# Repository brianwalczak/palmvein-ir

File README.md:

# palmvein-ir

An all-in-one IR illumination board for palm vein imaging, built using 16 high-power 860nm LEDs in two independently controlled channels.

## Why?

I built this board to serve as a second, more complete iteration of my original ir-led-board design [here](https://github.com/brianwalczak/ir-led-board). The main limitation of the first iteration was that it used 16 low-current IR LEDs, which made images less detailed because the infrared light didn't penetrate the palm effectively. The images were good for a proof-of-concept neural network but lacked the detail needed for a high detection accuracy. The square design also didn't accurately reflect the shape of an actual palm.

Another issue was the camera cutout. I decided to switch to the OV9281 for its global shutter and lack of a Bayer filter (which makes it the better camera for IR imaging). However, it uses a longer barrel lens, so the board needed a larger, circular camera cutout.

The board also lacked a position sensor, which made it difficult to calculate the palm's distance from the camera. For this first prototype, I tried to estimate palm distance using the average dimensions of a human palm, but I found out it was very unreliable, especially among varying age groups. I found that a distance sensor is the most reliable solution because adding an algorithm that estimates age range would honestly be way overengineered (and still unreliable among some people).

Finally, I added a dedicated microcontroller to handle the LED processing separately from the Raspberry Pi, which allows for precise LED flickering and switching without being affected by Linux delays!

## Features

I designed this board as an all-in-one solution to power and control the infrared LEDs, handle distance calculations, and to power the Raspberry Pi:

- 16x 860nm IR LEDs (OSRAM SFH 4718A) in two independently controlled channels
- Constant-current drivers (AL8861Y-13) with PWM brightness control, both running at about 909 mA
- Microcontroller (CH32V003) for LED control and channel switching
- Time-of-flight distance sensor (VL53L4CDV0DH/1) for measuring the palm's distance from the camera
- USB-C PD power at 20V, which also powers the Raspberry Pi 5 through a 5V buck converter
- Surge protector and eFuse for overvoltage and overcurrent protection

I chose USB-C over a fixed DC power supply because it's easier to use and more compact. The Raspberry Pi is powered through a custom JST cable connected to its 5V pins.

## Bill of Materials (BOM)

The key components for this project are listed below, but you can find the full BOM (including capacitors, resistors, etc.) [here](bom.csv).

| Qty | Component | Part |
|----:|-----------|------|
| 16 | 860nm IR LED | OSRAM SFH 4718A |
| 1 | Microcontroller | CH32V003A4M6 |
| 1 | Distance sensor | VL53L4CDV0DH/1 |
| 1 | USB-C PD trigger | CH224A |
| 1 | Pi buck converter (5V, 5A) | SY8366HQQC |
| 1 | 3.3V regulator | AMS1117-3.3 |
| 2 | LED driver | AL8861Y-13 |
| 1 | eFuse | MX25947ES |
| 1 | Surge protector (TDS) | TDS2211P.C(ES) |
| 1 | USB-C port | TYPE-C-31-M-12 |
| 1 | JST VH 6-pin connector | S6P-VH(LF)(SN)(P) |
| 1 | 4-pin programming header | PZ2.54-1x4PWZ-L13.8-A |

**Not included:** Raspberry Pi 5, OV9281-110 Camera, and a 65W+ USB-C PD charger.

## AI Usage

I used Claude Opus 5.5 to assist in routing the PCB, and to apply a few design fixes during the routing step.

## License

All hardware design files are released under the [CERN-OHL-P-2.0](LICENSE) license! Symbols, footprints, and 3D models were imported from EasyEDA using JLCImport and are not covered by this license.

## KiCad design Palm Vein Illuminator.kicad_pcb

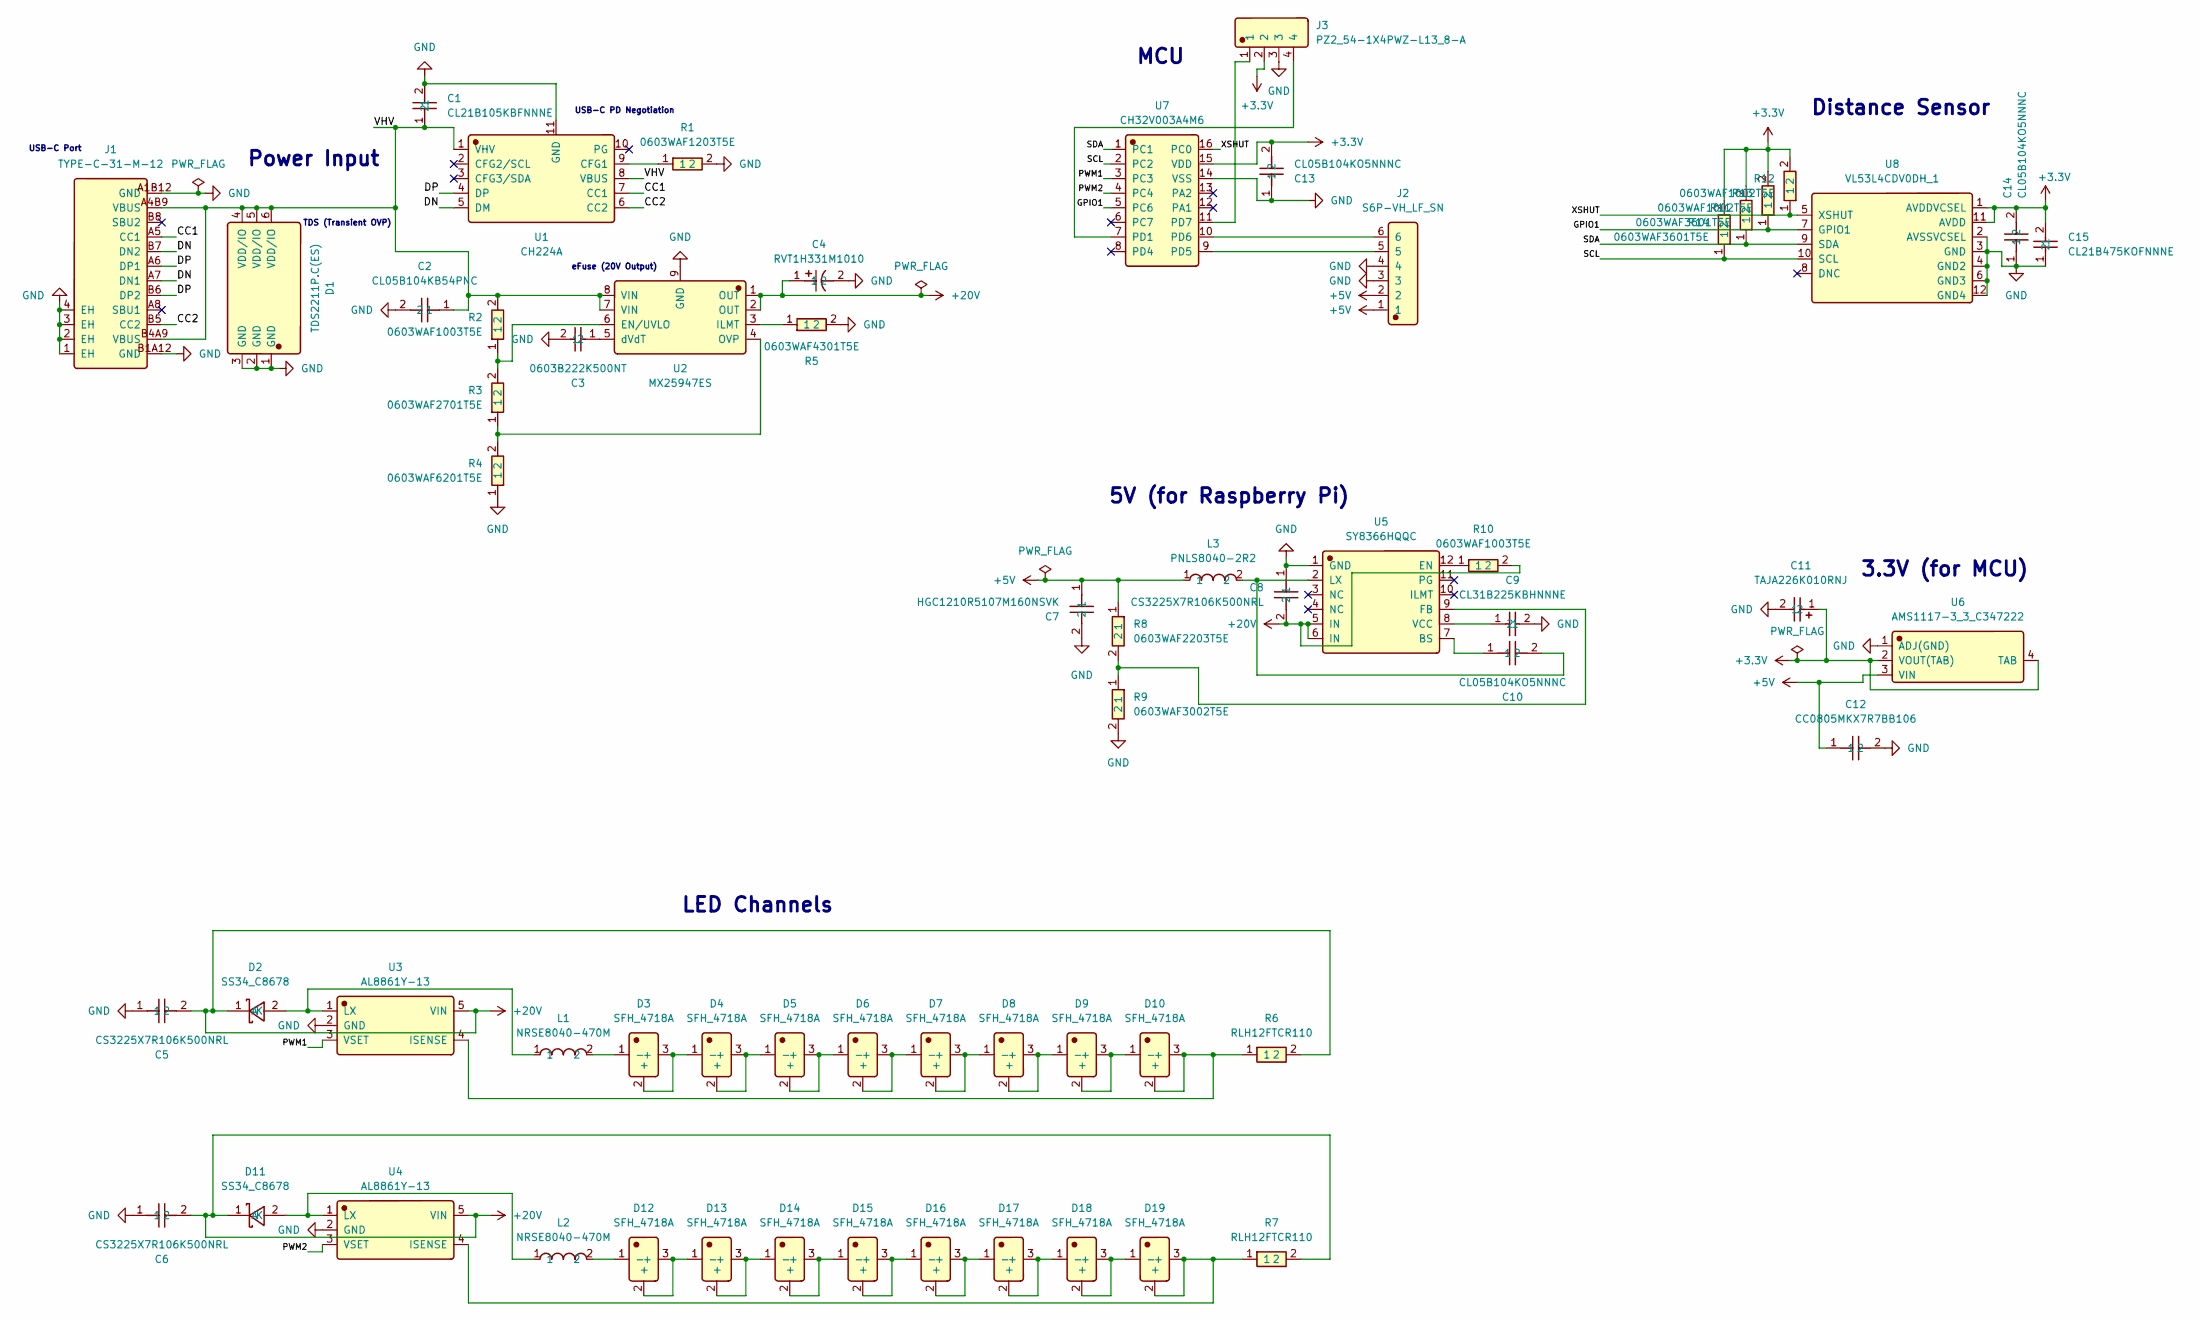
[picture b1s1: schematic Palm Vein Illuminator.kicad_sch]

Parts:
C1: CL21B105KBFNNNE; Manufacturer Part CL21B105KBFNNNE; LCSC C28323
C2: CL05B104KB54PNC; Manufacturer Part CL05B104KB54PNC; LCSC C307331
C3: 0603B222K500NT; Manufacturer Part 0603B222K500NT; LCSC C1604
C4: RVT1H331M1010; Manufacturer Part RVT1H331M1010 330UF 50V; LCSC C2687701
C5, C6, C8: CS3225X7R106K500NRL; Manufacturer Part CS3225X7R106K500NRL; LCSC C2918502
C7: HGC1210R5107M160NSVK; Manufacturer Part HGC1210R5107M160NSVK; LCSC C7432790
C9: CL31B225KBHNNNE; Manufacturer Part CL31B225KBHNNNE; LCSC C50254
C10, C13, C14: CL05B104KO5NNNC; Manufacturer Part CL05B104KO5NNNC; LCSC C1525
C11: TAJA226K010RNJ; Manufacturer Part TAJA226K010RNJ; LCSC C11366
C12: CC0805MKX7R7BB106; Manufacturer Part CC0805MKX7R7BB106; LCSC C1952587
C15: CL21B475KOFNNNE; Manufacturer Part CL21B475KOFNNNE; LCSC C107365
D1: TDS2211P.C(ES); Manufacturer Part TDS2211P.C(ES); LCSC C49108767
D2, D11: SS34_C8678; Manufacturer Part SS34; LCSC C8678
D3, D4, D5, D6, D7, D8, D9, D10, D12, D13, D14, D15, D16, D17, D18, D19: SFH_4718A; Manufacturer Part SFH 4718A; LCSC C2900417
J1: TYPE-C-31-M-12; Manufacturer Part TYPE-C-31-M-12; LCSC C165948
J2: S6P-VH_LF_SN; Manufacturer Part S6P-VH(LF)(SN)(P); LCSC C495698
J3: PZ2_54-1X4PWZ-L13_8-A; Manufacturer Part PZ2.54-1x4PWZ-L13.8-A; LCSC C54907647
L1, L2: NRSE8040-470M; Manufacturer Part NRSE8040-470M; LCSC C2903105
L3: PNLS8040-2R2; Manufacturer Part PNLS8040-2R2M 2.2UH; LCSC C2849550
R1: 0603WAF1203T5E; Manufacturer Part 0603WAF1203T5E; LCSC C25808
R2, R10: 0603WAF1003T5E; Manufacturer Part 0603WAF1003T5E; LCSC C25803
R3: 0603WAF2701T5E; Manufacturer Part 0603WAF2701T5E; LCSC C13167
R4: 0603WAF6201T5E; Manufacturer Part 0603WAF6201T5E; LCSC C4260
R5: 0603WAF4301T5E; Manufacturer Part 0603WAF4301T5E; LCSC C23159
R6, R7: RLH12FTCR110; Manufacturer Part RLH12FTCR110; LCSC C22464898
R8: 0603WAF2203T5E; Manufacturer Part 0603WAF2203T5E; LCSC C22961
R9: 0603WAF3002T5E; Manufacturer Part 0603WAF3002T5E; LCSC C22984
R11, R14: 0603WAF3601T5E; Manufacturer Part 0603WAF3601T5E; LCSC C22980
R12, R13: 0603WAF1002T5E; Manufacturer Part 0603WAF1002T5E; LCSC C25804
U1: CH224A; Manufacturer Part CH224A; LCSC C42459160
U2: MX25947ES; Manufacturer Part MX25947ES; LCSC C5875698
U3, U4: AL8861Y-13; Manufacturer Part AL8861Y-13; LCSC C507867
U5: SY8366HQQC; Manufacturer Part SY8366HQQC; LCSC C178253
U6: AMS1117-3_3_C347222; Manufacturer Part AMS1117-3.3; LCSC C347222
U7: CH32V003A4M6; Manufacturer Part CH32V003A4M6; LCSC C5346357
U8: VL53L4CDV0DH_1; Manufacturer Part VL53L4CDV0DH/1; LCSC C3178291

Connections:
+3.3V: C11.1, C13.2, C14.2, C15.2, J3.2, R11.2, R12.2, R13.2, R14.2, U6.2 (VOUT(TAB)), U6.4 (TAB), U7.15 (VDD), U8.1 (AVDDVCSEL), U8.11 (AVDD)
+5V: C7.1, C12.1, J2.1, J2.2, L3.1, R8.1, U6.3 (VIN)
+20V: C4.1, C5.2, C6.2, C8.2, D2.1 (K), D11.1 (K), R6.2, R7.2, R10.2, U2.1 (OUT), U2.2 (OUT), U3.5 (VIN), U4.5 (VIN), U5.5 (IN), U5.6 (IN)
/CC1: J1.A5 (CC1), U1.7 (CC1)
/CC2: J1.B5 (CC2), U1.6 (CC2)
/DN: J1.A7 (DN1), J1.B7 (DN2), U1.5 (DM)
/DP: J1.A6 (DP1), J1.B6 (DP2), U1.4 (DP)
/GPIO1: R13.1, U7.5 (PC6), U8.7 (GPIO1)
/PWM1: U3.3 (VSET), U7.3 (PC3)
/PWM2: U4.3 (VSET), U7.4 (PC4)
/SCL: R14.1, U7.2 (PC2), U8.10 (SCL)
/SDA: R11.1, U7.1 (PC1), U8.9 (SDA)
/VHV: C1.1, C2.1, D1.4 (VDD/IO), D1.5 (VDD/IO), D1.6 (VDD/IO), J1.A4B9 (VBUS), J1.B4A9 (VBUS), R2.2, U1.1 (VHV), U1.8 (VBUS), U2.7 (VIN), U2.8 (VIN)
/XSHUT: R12.1, U7.16 (PC0), U8.5 (XSHUT)
GND: C1.2, C2.2, C3.2, C4.2, C5.1, C6.1, C7.2, C8.1, C9.2, C11.2, C12.2, C13.1, C14.1, C15.1, D1.1 (GND), D1.2 (GND), D1.3 (GND), J1.1 (EH), J1.2 (EH), J1.3 (EH), J1.4 (EH), J1.A1B12 (GND), J1.B1A12 (GND), J2.3, J2.4, J3.3, R1.2, R4.1, R5.2, R9.2, U1.11 (GND), U2.9 (GND), U3.2 (GND), U4.2 (GND), U5.1 (GND), U6.1 (ADJ(GND)), U7.14 (VSS), U8.2 (AVSSVCSEL), U8.3 (GND), U8.4 (GND2), U8.6 (GND3), U8.12 (GND4)
unnamed: D2.2 (A), L1.1, U3.1 (LX)
unnamed: D3.1 (-), L1.2
unnamed: D3.2 (+), D3.3 (+), D4.1 (-)
unnamed: D4.2 (+), D4.3 (+), D5.1 (-)
unnamed: D5.2 (+), D5.3 (+), D6.1 (-)
unnamed: D6.2 (+), D6.3 (+), D7.1 (-)
unnamed: D7.2 (+), D7.3 (+), D8.1 (-)
unnamed: D8.2 (+), D8.3 (+), D9.1 (-)
unnamed: D9.2 (+), D9.3 (+), D10.1 (-)
unnamed: D11.2 (A), L2.1, U4.1 (LX)
unnamed: D12.1 (-), L2.2
unnamed: D12.2 (+), D12.3 (+), D13.1 (-)
unnamed: D13.2 (+), D13.3 (+), D14.1 (-)
unnamed: D14.2 (+), D14.3 (+), D15.1 (-)
unnamed: D15.2 (+), D15.3 (+), D16.1 (-)
unnamed: D16.2 (+), D16.3 (+), D17.1 (-)
unnamed: D17.2 (+), D17.3 (+), D18.1 (-)
unnamed: D18.2 (+), D18.3 (+), D19.1 (-)
unnamed: R1.1, U1.9 (CFG1)
unnamed: R2.1, R3.2, U2.6 (EN/UVLO)
unnamed: R5.1, U2.3 (ILMT)
unnamed: R3.1, R4.2, U2.4 (OVP)
unnamed: C3.1, U2.5 (dVdT)
unnamed: D10.2 (+), D10.3 (+), R6.1, U3.4 (ISENSE)
unnamed: D19.2 (+), D19.3 (+), R7.1, U4.4 (ISENSE)
unnamed: C10.1, U5.7 (BS)
unnamed: R10.1, U5.12 (EN)
unnamed: R8.2, R9.1, U5.9 (FB)
unnamed: C10.2, L3.2, U5.2 (LX)
unnamed: C9.1, U5.8 (VCC)
unnamed: J3.4, U7.7 (PD1)
unnamed: J2.5, U7.9 (PD5)
unnamed: J2.6, U7.10 (PD6)
unnamed: J3.1, U7.11 (PD7)

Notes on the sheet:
eFuse (20V Output)
Distance Sensor
TDS (Transient OVP)
3.3V (for MCU)
USB-C Port
LED Channels
5V (for Raspberry Pi)
Power Input
MCU
USB-C PD Negotiation

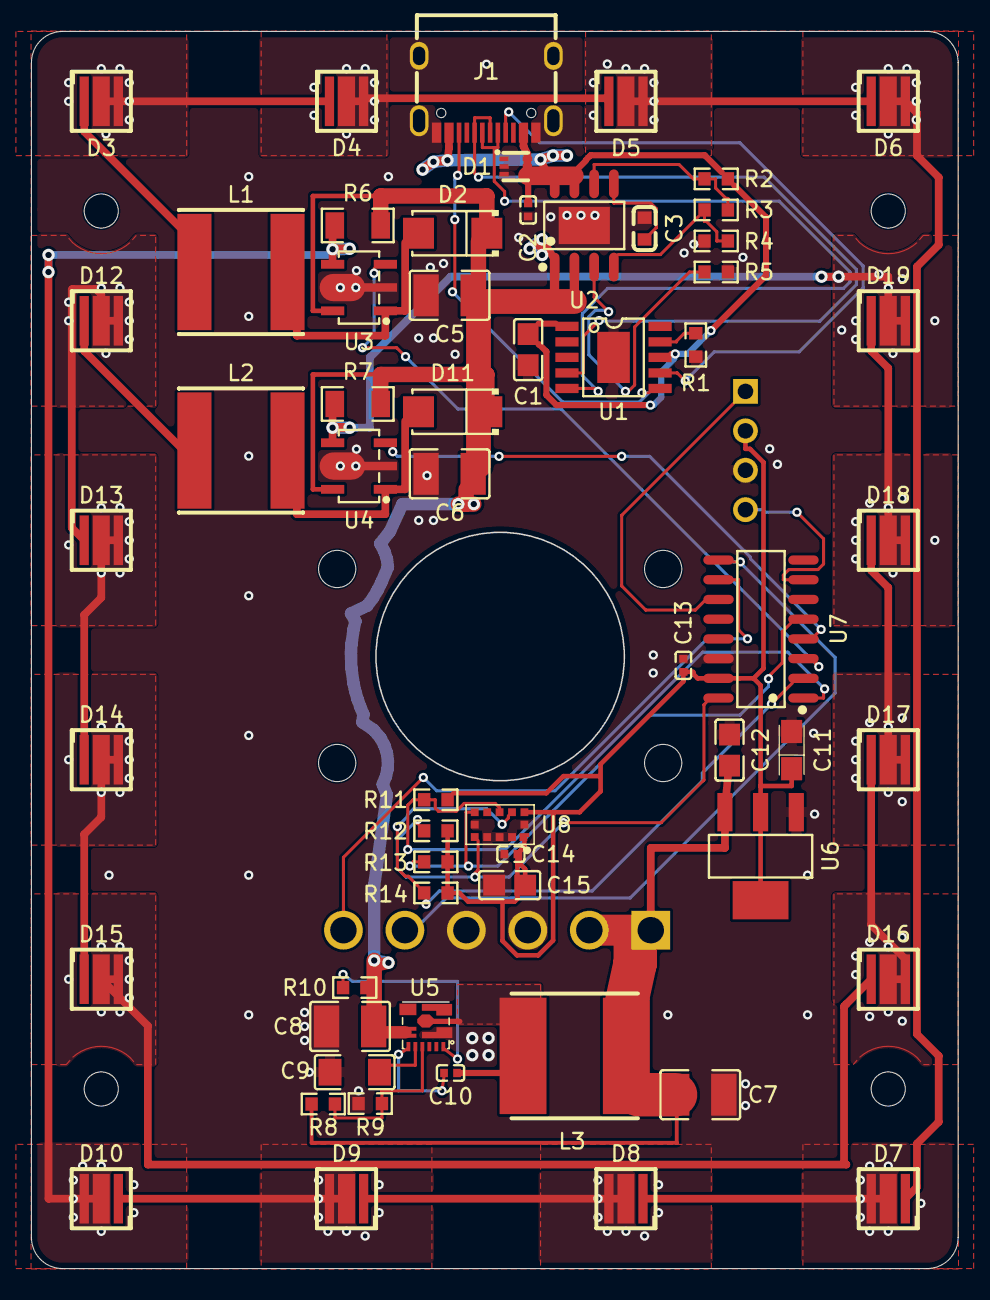
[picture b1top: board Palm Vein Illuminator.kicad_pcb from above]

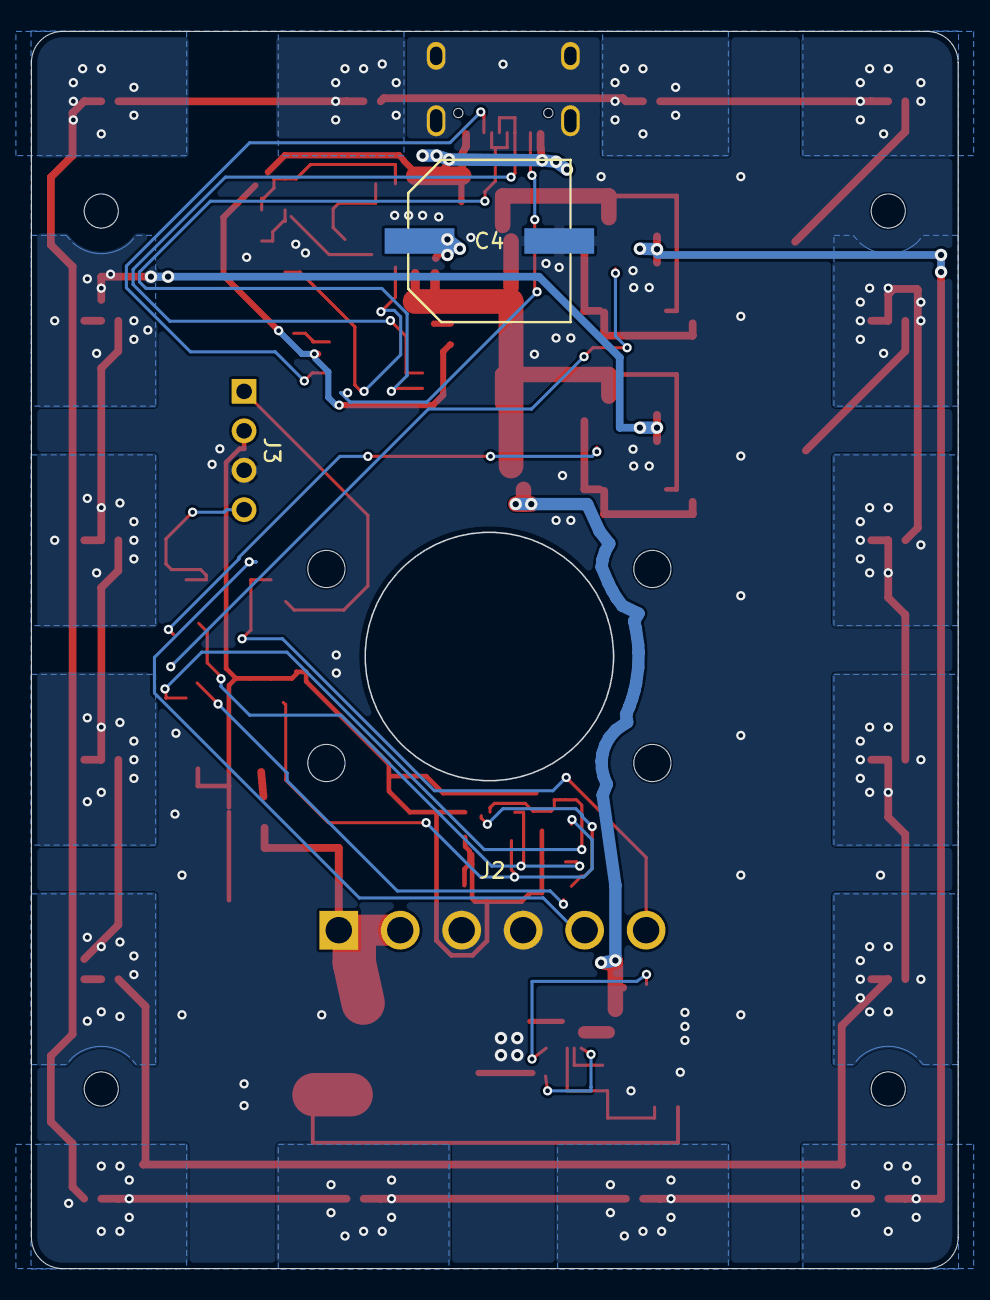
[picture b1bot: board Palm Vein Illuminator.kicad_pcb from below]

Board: 2 copper layers, 59.7 x 79.7 mm, 70 parts (3 on the bottom side), 49 nets.

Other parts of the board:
H1, H2, H3, H4, H5, H6, H7, H8: MountingHole_2.2mm_M2

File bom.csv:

"Reference","Qty","Manufacturer Part","Description","Manufacturer","LCSC"
"C1","1","CL21B105KBFNNNE","1uF 50V X7R ±10% 0805 Multilayer Ceramic Capacitors MLCC - SMD/SMT ROHS","Samsung Electro-Mechanics","C28323"
"C2","1","CL05B104KB54PNC","100nF 50V X7R ±10% 0402 Multilayer Ceramic Capacitors MLCC - SMD/SMT ROHS","Samsung Electro-Mechanics","C307331"
"C3","1","0603B222K500NT","2.2nF 50V X7R ±10% 0603 Multilayer Ceramic Capacitors MLCC - SMD/SMT ROHS","FH (Guangdong Fenghua Advanced Tech)","C1604"
"C4","1","RVT1H331M1010 330UF 50V","-55℃~+105℃ 10.2mm 10mm 2800hrs@105℃ 330uF 50V ±20% SMD,D10xL10.2mm Aluminum Electrolytic Capacitors - SMD ROHS","DMBJ","C2687701"
"C5,C6,C8","3","CS3225X7R106K500NRL","10uF 50V X7R 1210 Multilayer Ceramic Capacitors MLCC - SMD/SMT ROHS","Samwha Capacitor","C2918502"
"C7","1","HGC1210R5107M160NSVK","100uF 16V X5R ±20% 1210 Multilayer Ceramic Capacitors MLCC - SMD/SMT ROHS","Chinocera","C7432790"
"C9","1","CL31B225KBHNNNE","2.2uF 50V X7R ±10% 1206 Multilayer Ceramic Capacitors MLCC - SMD/SMT ROHS","Samsung Electro-Mechanics","C50254"
"C10,C13,C14","3","CL05B104KO5NNNC","100nF 16V X7R ±10% 0402 Multilayer Ceramic Capacitors MLCC - SMD/SMT ROHS","Samsung Electro-Mechanics","C1525"
"C11","1","TAJA226K010RNJ","-55℃~+125℃ 10V 22uF 3Ω@100kHz ±10% CASE-A-3216-18(mm) Tantalum Capacitors ROHS","--","C11366"
"C12","1","CC0805MKX7R7BB106","10uF 16V X7R ±20% 0805 Multilayer Ceramic Capacitors MLCC - SMD/SMT ROHS","YAGEO","C1952587"
"C15","1","CL21B475KOFNNNE","16V 4.7uF X7R ±10% 0805 Multilayer Ceramic Capacitors MLCC - SMD/SMT ROHS","Samsung Electro-Mechanics","C107365"
"D1","1","TDS2211P.C(ES)","-40℃~+125℃ 1 1.967kW@8/20us 115pF 22V 25.6V 28.1V 500pA 70A@8/20us IEC 61000-4-2 DFN1616-6L ESD and Surge Protection (TVS/ESD) ROHS","ElecSuper","C49108767"
"D2,D11","2","SS34","-55℃~+125℃ 3A 40V 500uA@40V 550mV@3A Independent SMA(DO-214AC) Schottky Diodes ROHS","MDD(Microdiode Semiconductor)","C8678"
"D3,D4,D5,D6,D7,D8,D9,D10,D12,D13,D14,D15,D16,D17,D18,D19","16","SFH 4718A","-40℃~+125℃ 1.75V 400mW/sr@IF=1A 860nm SMD-3P Infrared LED Emitters ROHS","OSRAM Opto Semicon","C2900417"
"J1","1","TYPE-C-31-M-12","-30℃~+80℃ 1 10,000 cycles 16P 20V 5A 7.35mm Female Surface Mount, Right Angle Type-C SMD USB Connectors ROHS","Korean Hroparts Elec","C165948"
"J2","1","S6P-VH(LF)(SN)(P)","-25℃~+85℃ 1 10A 13.9mm 1x6P 23.7mm 250V 3.96mm 6 6P Brass PA66 Right Angle Tin UL94V-0 VH White 弯插,P=3.96mm Wire To Board Connector ROHS","JST","C495698"
"J3","1","PZ2.54-1x4PWZ-L13.8-A","-40℃~+105℃ 1 1x4P 2.54mm 2.54mm 2.5mm 250V 3A 3mm 4P 6mm Black Brass Gold Pin Header Right Angle 弯插,P=2.54mm Pin Headers ROHS","SHOU HAN","C54907647"
"L1,L2","2","NRSE8040-470M","1.5A 1.75A 158mΩ 47uH Magnetic Shielded Inductor ±20% SMD,8x8mm Power Inductors ROHS","KOHERelec","C2903105"
"L3","1","PNLS8040-2R2M 2.2UH","12mΩ 2.2uH 8A 8A Magnetic Shielded Inductor ±20% SMD,8x8mm Power Inductors ROHS","DMBJ","C2849550"
"R1","1","0603WAF1203T5E","-55℃~+155℃ 100mW 120kΩ 75V Thick Film Resistor ±1% ±100ppm/℃ 0603 Chip Resistor - Surface Mount ROHS","UNI-ROYAL(Uniroyal Elec)","C25808"
"R2,R10","2","0603WAF1003T5E","-55℃~+155℃ 100kΩ 100mW 75V Thick Film Resistor ±1% ±100ppm/℃ 0603 Chip Resistor - Surface Mount ROHS","UNI-ROYAL(Uniroyal Elec)","C25803"
"R3","1","0603WAF2701T5E","-55℃~+155℃ 100mW 2.7kΩ 75V Thick Film Resistor ±1% ±100ppm/℃ 0603 Chip Resistor - Surface Mount ROHS","UNI-ROYAL(Uniroyal Elec)","C13167"
"R4","1","0603WAF6201T5E","-55℃~+155℃ 100mW 6.2kΩ 75V Thick Film Resistor ±1% ±100ppm/℃ 0603 Chip Resistor - Surface Mount ROHS","UNI-ROYAL(Uniroyal Elec)","C4260"
"R5","1","0603WAF4301T5E","-55℃~+155℃ 100mW 4.3kΩ 75V Thick Film Resistor ±1% ±100ppm/℃ 0603 Chip Resistor - Surface Mount ROHS","UNI-ROYAL(Uniroyal Elec)","C23159"
"R6,R7","2","RLH12FTCR110","110mΩ 1W Current Sense Resistor SMD ±1% ±100ppm/℃ 1206 Current Sense Resistors / Shunt Resistors ROHS","TA-I Tech","C22464898"
"R8","1","0603WAF2203T5E","-55℃~+155℃ 100mW 220kΩ 75V Thick Film Resistor ±1% ±100ppm/℃ 0603 Chip Resistor - Surface Mount ROHS","UNI-ROYAL(Uniroyal Elec)","C22961"
"R9","1","0603WAF3002T5E","-55℃~+155℃ 100mW 30kΩ 75V Thick Film Resistor ±1% ±100ppm/℃ 0603 Chip Resistor - Surface Mount ROHS","UNI-ROYAL(Uniroyal Elec)","C22984"
"R11,R14","2","0603WAF3601T5E","-55℃~+155℃ 100mW 3.6kΩ 75V Thick Film Resistor ±1% ±100ppm/℃ 0603 Chip Resistor - Surface Mount ROHS","UNI-ROYAL(Uniroyal Elec)","C22980"
"R12,R13","2","0603WAF1002T5E","-55℃~+155℃ 100mW 10kΩ 75V Thick Film Resistor ±1% ±100ppm/℃ 0603 Chip Resistor - Surface Mount ROHS","UNI-ROYAL(Uniroyal Elec)","C25804"
"U1","1","CH224A","-40℃~+105℃ 140W 1C 4V~30V 5V、9V、12V、15V、20V、28V PD 3.2、BC 1.2、AVS、PPS、SPR Power Receiver Controller ESSOP-10 USB PD ROHS","WCH(Jiangsu Qin Heng)","C42459160"
"U2","1","MX25947ES","-40℃~+125℃ 1 1.4mm 28mΩ 3.9mm 4.5V~24V 4.9mm Integrated FET Surface Mount ESOP8 Surge Protection Devices (SPDs) ROHS","Wuxi Maxinmicro","C5875698"
"U3,U4","2","AL8861Y-13","-40℃~+85℃ 1 1.5A 1MHz 4.5V~40V 5% Analog、PWM Buck Built-in DC-DC Over-Temperature Protection (OTP)、Short-Circuit  Protection SOT-89-5 LED Drivers ROHS","Diodes Incorporated","C507867"
"U5","1","SY8366HQQC","-40℃~+150℃ 1 100uA 4V~28V 5V 6A 800kHz Buck Buck Built-in Fixed Yes QFN-12-EP(3x3) DC-DC Converters ROHS","Silergy Corp","C178253"
"U6","1","AMS1117-3.3","-40℃~+125℃ 0.003%Vout 1 1.3V@(1A) 12V 1A 3.3V 5mA 60dB@(120Hz) Fixed Over Current Protection Positive SOT-223 Voltage Regulators - Linear, Low Drop Out (LDO) Regulators ROHS","UMW(Youtai Semiconductor Co., Ltd.)","C347222"
"U7","1","CH32V003A4M6","SOP-16 Microcontrollers (MCU/MPU/SOC) ROHS","WCH(Jiangsu Qin Heng)","C5346357"
"U8","1","VL53L4CDV0DH/1","-30℃~+85℃ 0cm~130cm 1mm 2.4mm 2.6V~3.5V 24mA 4.4mm I2C Temperature compensation Yes SMD-12P Position Sensors ROHS","STMicroelectronics","C3178291"
